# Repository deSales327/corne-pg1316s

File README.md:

# corne-pg1316s

PCB reversível e sem fios no formato **Corne** (3×6 + 3 polegares por metade, 42 teclas)
para os switches ultrafinos **Kailh PG1316S**, com **um LED RGB por tecla** e keycaps impressas
em 3D (do [mikefive](https://github.com/mikeholscher/zmk-config-mikefive)) ou compradas, e **nice!nano + nice!view**. É a versão "irmã" do
[corne-x](https://github.com/deSales327/corne-x), que usa switches Kailh X (PG1425).

| Frente | Verso |
| :---: | :---: |
|  |  |

## Estado
- Roteada nas duas camadas, com plano de GND.
- **DRC do KiCad 10: 0 violações e 0 ligações em falta.**
- Gerbers e furação prontos em [`corne-pg1316s-gerbers.zip`](corne-pg1316s-gerbers.zip).
- **Ainda não foi fabricada nem testada.** Há footprints de PG1316S já fabricados com os contactos em sítios diferentes: x = ±2,5 mm (ficha técnica, [mikefive](https://github.com/mikeholscher/zmk-config-mikefive), [ULK](https://github.com/Goga64/ULK)) e x = −0,5 / +1,7 mm ([Delta Omega](https://github.com/unspecworks/delta-omega) rev4). Os terminais do switch são largos o suficiente para os dois. Mesmo assim, confirma com um switch físico (por exemplo, numa impressão 1:1) antes de encomendar.
- **v0.5:** o XIAO deu lugar a um Pro Micro nRF52840 (nice!nano v2 ou clone) com a pinagem do Corne do ZMK, e há furos para um nice!view por cima dele. Os LEDs são desligados por software (VCC do nice!nano), por isso o interruptor RGB1 saiu. Foi acrescentado um botão de reset. Usa os gerbers da v0.5.
- **v0.4:** um LED RGB WS2812B-2020 por tecla, na cavidade debaixo do switch. Os díodos passaram para o intervalo entre colunas, na face de baixo.
- **v0.3:** os pads de contacto são largos e cobrem as duas posições testadas: o pad 1 vai de −3,275 a −0,025 mm e o pad 2 de +0,925 a +3,275 mm, como no footprint reversível do mikefive. No verso ficam espelhados.

## Componentes (por metade)
| Qtd. | Peça |
|---|---|
| 21 | Kailh PG1316S (SMD) |
| 21 | LED RGB WS2812B-2020 (2 × 2 mm) |
| 21 | Díodo 1N4148W, SOD-123 |
| 1 | Pro Micro nRF52840: nice!nano v2 ou clone compatível (ex.: SuperMini nRF52840) com corte de VCC no P0.13 |
| 1 | nice!view (ecrã de 1,08", 36 × 14 mm), com o conector e os pinos que trazem |
| 2 | Barras de 12 pinos fêmea + pinos macho baixos (para o controlador) |
| 1 | Interruptor SPDT (o mesmo do dust) |
| 1 | Botão Omron B3U-1000P (reset) |
| 1 | Conector JST-XH 2,50 mm, vertical, 2 pinos |
| 1 | Bateria LiPo com ficha JST-XH (quanto maior, melhor, por causa dos LEDs) |
| 21 | Keycaps: Kailh PG1316 1U transparentes (16 × 16 mm, ex.: Modulo "Clear") para se ver a luz, ou as impressas de [`keycaps/`](keycaps/) |
| 4+ | Pés de borracha com 1,5 mm ou mais (os díodos ficam por baixo) |

## Diferenças para o corne-x
- **Espaçamento de 17 × 17 mm** para keycaps de 16,5 × 16,5 mm. Cada metade mede 128,5 × 83,9 mm.
- **Footprint PG1316S reversível**, desenhado em `gerar_pcb.py`:
  - O chassi e os furos seguem a ficha técnica `CPG1316S01D02`.
  - Os contactos são largos e cobrem as posições dos footprints testados do mikefive, do ULK e do Delta Omega.
  - Os terminais do switch não são simétricos, por isso os contactos têm pads próprios em cada face, espelhados no verso, e as pistas ligam-nos entre si.
  - Os pads do chassi têm um furo metalizado e servem as duas faces.
  - Há furos para os pinos de alinhamento das duas faces.
- **LED na cavidade debaixo do switch**, que é a janela de LED da ficha técnica. Os pads existem nas duas faces; o LED vai na mesma face que o switch.
- **Díodos entre colunas, na face oposta à do switch** (a de baixo). Os pads existem nas duas faces; na face do switch ficam vazios.
- **Soldadura**, por esta ordem, em cada metade:
  1. LEDs e switches na face de cima (numa metade é a frente, na outra o verso), com pasta de solda e placa de aquecimento (hotplate). Os LEDs de 2 × 2 mm são difíceis de soldar com ferro.
  2. Díodos na face de baixo, com ferro de soldar (não voltes a pôr a placa na hotplate com peças por baixo).
  3. Botão de reset na face de cima, também com ferro.
  4. Controlador, nice!view, interruptor e conector.
  - Testa os LEDs antes de soldar os switches por cima: depois deixam de estar acessíveis.

## Bateria
- **J1**: JST-XH 2,50 mm vertical, de furos passantes. O pino 1 é o BAT+ e o pino 2 o BAT−.
- **H1**: furo de 3,2 mm para passar os fios da bateria, que fica por baixo da placa.
- **PWR1**: interruptor no BAT−.
- O BAT+ liga ao pino RAW do nice!nano v2, que é a entrada da bateria (e passa pelo carregador dele).
- Atenção à altura: o JST-XH vertical tem cerca de 7 mm, muito mais do que o resto do teclado.

## Controlador e nice!view
- **MCU1**: Pro Micro reversível sem pontes de solda. Os furos são os mesmos nas duas faces:
  - na metade em que a placa tem a **frente para cima**, o controlador monta-se com os **componentes para cima**;
  - na metade em que a placa tem o **verso para cima**, monta-se com os **componentes para baixo** (como no Corne). Assim cada pino cai sempre no mesmo furo. Está escrito no silkscreen de cada face.
- **DISP1**: duas filas de 5 furos para o nice!view, logo abaixo do controlador. A fila de cima é para a metade com a frente para cima e a de baixo para a outra (a ordem dos pinos fica invertida quando a placa se vira). O ecrã fica por cima do controlador.
- **RST1**: botão de reset (duplo toque entra no bootloader). Há pads nas duas faces; solda-se só o da face de cima.
- Altura: com o nice!view por cima, o bloco do controlador fica bem mais alto do que as teclas (cerca de 7–10 mm, conforme os pinos e as barras que usares).

## Pinos do Pro Micro
Iguais aos do Corne do ZMK, por isso servem os shields `corne_left`/`corne_right` sem alterações.

| Pino | Função | Pino | Função |
|---|---|---|---|
| D1 (P0.06) | nice!view CS | RAW | BAT+ (via J1) |
| D0 (P0.08) | dados dos LEDs RGB | GND | GND |
| GND | GND | RST | botão de reset |
| GND | GND | VCC | 3,3 V comutado (LEDs e nice!view) |
| D2 (P0.17) | nice!view MOSI | D21 | c0 (mindinho externo) |
| D3 (P0.20) | nice!view SCK | D20 | c1 (mindinho) |
| D4 | r3 (fila de cima) | D19 | c2 (anelar) |
| D5 | r2 (fila home) | D18 | c3 (médio) |
| D6 | r1 (fila de baixo) | D15 | c4 (indicador) |
| D7 | r0 (polegares) | D14 | c5 (indicador interno) |
| D8 | livre | D16 | livre |
| D9 | livre | D10 | livre |

- O cátodo dos díodos (pad 1) fica na linha: COL2ROW, como no Corne.
- Os polegares usam as colunas c3, c4 e c5 da linha r0 (`RC(3,3)`, `RC(3,4)`, `RC(3,5)`).

## LEDs RGB
- **L1–L21**: WS2812B-2020, um por tecla, em cadeia: D0 → polegares (de dentro para fora) → colunas em serpentina, da interna (c5) para a externa (c0).
- Alimentados pelo **VCC do nice!nano** (3,3 V), que o ZMK corta quando os LEDs estão desligados ou o teclado em repouso (`ext-power`, P0.13). Os LEDs gastam corrente mesmo apagados, por isso este corte é importante.
- 3,3 V está abaixo dos 3,7 V da ficha técnica dos WS2812B-2020. É como muitos Corne sem fios com nice!nano funcionam, mas o azul e o branco podem ficar um pouco mais fracos.
- **Limita o brilho no firmware.** O VCC do nice!nano não aguenta os 21 LEDs a branco no máximo.

## ZMK
No `build.yaml` do teu zmk-config:

```yaml
include:
  - board: nice_nano_v2
    shield: corne_left nice_view_adapter nice_view
  - board: nice_nano_v2
    shield: corne_right nice_view_adapter nice_view
```

(Nas versões mais recentes do ZMK a placa chama-se `nice_nano` em vez de `nice_nano_v2`.)

Para os LEDs, num `corne.overlay` (ou `corne_left.overlay` e `corne_right.overlay`) na pasta `config`:

```dts
#include <dt-bindings/led/led.h>

&pinctrl {
    spi3_default: spi3_default {
        group1 { psels = <NRF_PSEL(SPIM_MOSI, 0, 8)>; };
    };
    spi3_sleep: spi3_sleep {
        group1 { psels = <NRF_PSEL(SPIM_MOSI, 0, 8)>; low-power-enable; };
    };
};

&spi3 {
    compatible = "nordic,nrf-spim";
    status = "okay";
    pinctrl-0 = <&spi3_default>;
    pinctrl-1 = <&spi3_sleep>;
    pinctrl-names = "default", "sleep";
    led_strip: ws2812@0 {
        compatible = "worldsemi,ws2812-spi";
        reg = <0>;
        spi-max-frequency = <4000000>;
        chain-length = <21>;
        spi-one-frame = <0x70>;
        spi-zero-frame = <0x40>;
        color-mapping = <LED_COLOR_ID_GREEN LED_COLOR_ID_RED LED_COLOR_ID_BLUE>;
    };
};

/ { chosen { zmk,underglow = &led_strip; }; };
```

No `corne.conf`:

```
CONFIG_ZMK_RGB_UNDERGLOW=y
CONFIG_WS2812_STRIP=y
CONFIG_ZMK_RGB_UNDERGLOW_EXT_POWER=y
CONFIG_ZMK_RGB_UNDERGLOW_BRT_MAX=40
CONFIG_ZMK_RGB_UNDERGLOW_AUTO_OFF_IDLE=y
```
## Regenerar
```
python gerar_pcb.py caminho/para/dust/pcbs/dust.kicad_pcb
"%LOCALAPPDATA%\Programs\KiCad\10.0\bin\python.exe" finalizar_pcb.py caminho/para/freerouting-2.5.0.jar
python mockup.py
```
Precisas do `shapely` (pip), do KiCad 10, do Freerouting 2.5 e do Java 25.

## Créditos
- Díodo e interruptor: [dust](https://github.com/hazels-garage/dust), de Jason Hazel (CC BY 4.0).
- Keycaps e referência do PG1316S: [mikefive](https://github.com/mikeholscher/zmk-config-mikefive), de Mike Holscher. Uso permitido com crédito ao autor.
- Footprint do switch: desenhado a partir da ficha técnica da Kailh (CPG1316S01D02). As posições dos contactos foram comparadas com o [Delta Omega](https://github.com/unspecworks/delta-omega), de unspecworks (CERN-OHL-W-2.0), e com o [ULK](https://github.com/Goga64/ULK), de Georgii Miakishev (MIT), um Corne com PG1316S já construído.
- Lojas de PG1316S indicadas pelo Delta Omega (não verificadas): Modulo Industries (EUA), Holykeebs (EUA) e Keycapsss (UE).
- Layout: Corne (crkbd), de foostan (MIT).
- Este projeto: CC BY 4.0, exceto as keycaps, que seguem as condições do autor.

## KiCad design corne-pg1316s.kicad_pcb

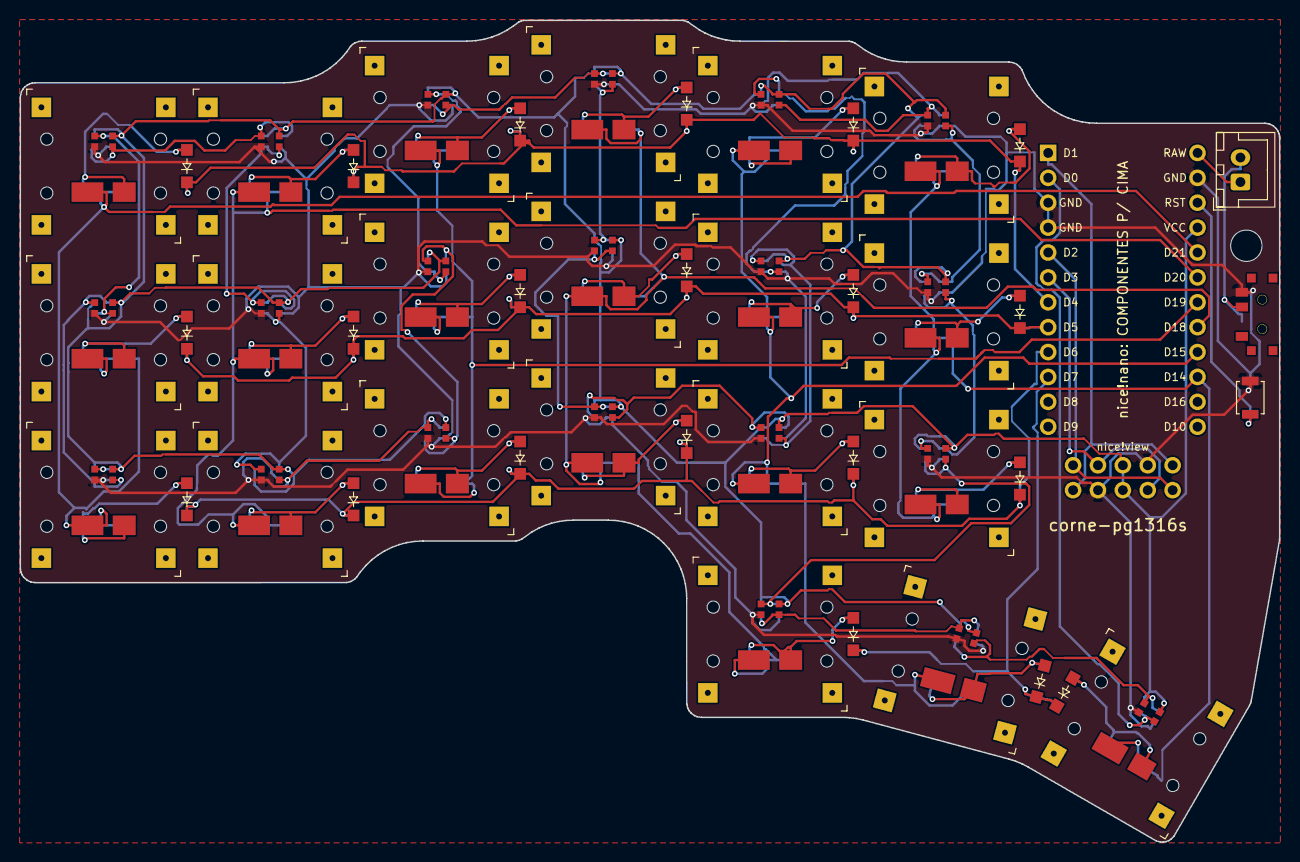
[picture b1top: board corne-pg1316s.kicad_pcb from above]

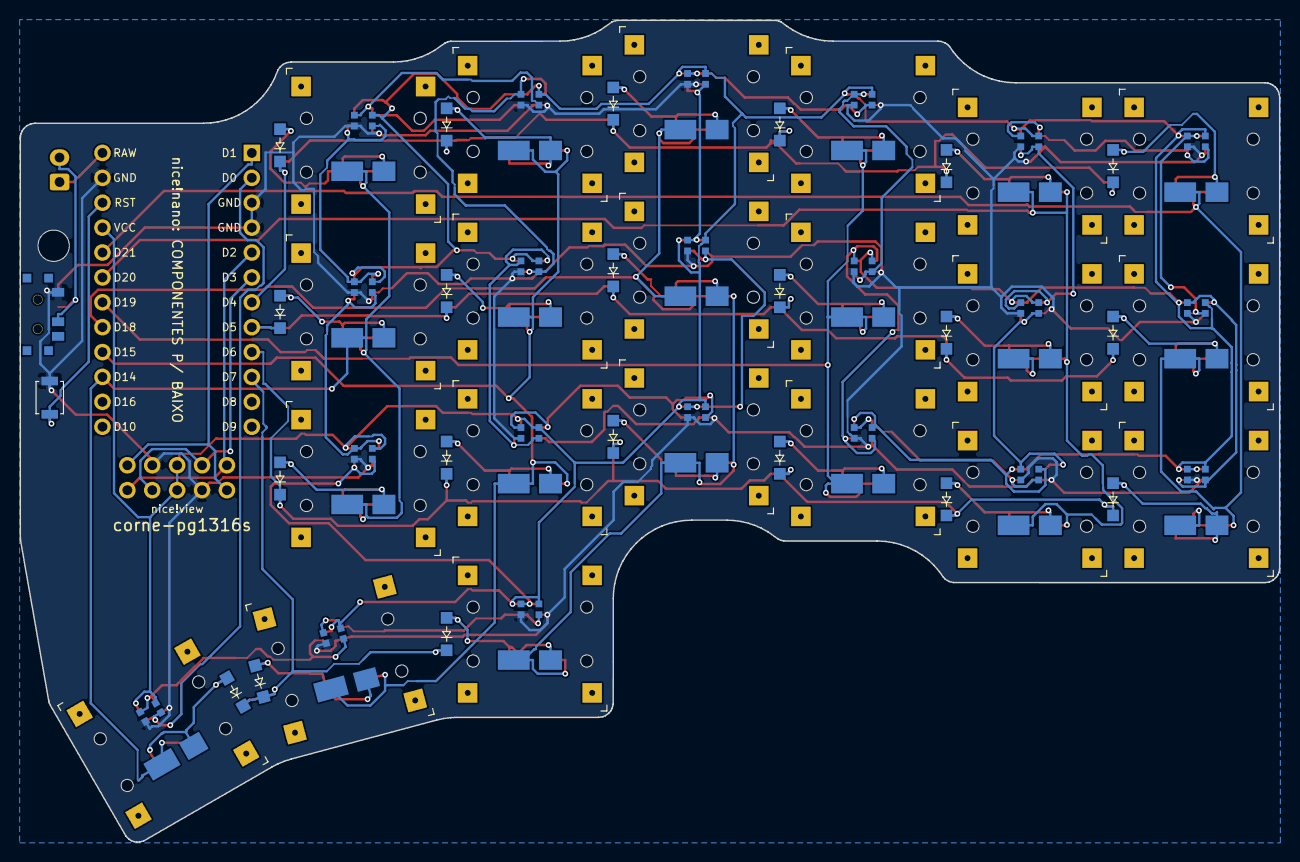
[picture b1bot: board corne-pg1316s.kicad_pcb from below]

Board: 2 copper layers, 128.5 x 83.9 mm, 71 parts (2 on the bottom side), 60 nets.

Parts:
D1, D2, D3, D4, D5, D6, D7, D8, D9, D10, D11, D12, D13, D14, D15, D16, D17, D18, D19, D20, D21: ComboDiode
DISP1: nice_view_reversible
H1: MountingHole_3.2mm_M3
J1: JST_XH_B2B-XH-A_1x02_P2.50mm_Vertical
L1, L2, L3, L4, L5, L6, L7, L8, L9, L10, L11, L12, L13, L14, L15, L16, L17, L18, L19, L20, L21: WS2812B-2020; WS2812B-2020_reversible
MCU1: ProMicro_reversible
PWR1, PWR1#2: SPDT_C128955
RST1, RST2: SW_SPST_B3U-1000P
S1, S2, S3, S4, S5, S6, S7, S8, S9, S10, S11, S12, S13, S14, S15, S16, S17, S18, S19, S20, S21: PG1316S; Kailh_PG1316S_reversible

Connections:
BAT: J1.1, MCU1.13
BAT-: J1.2, PWR1.2, PWR1#2.2
GND: DISP1.4, DISP1.7, L1.2, L2.2, L3.2, L4.2, L5.2, L6.2, L7.2, L8.2, L9.2, L10.2, L11.2, L12.2, L13.2, L14.2, L15.2, L16.2, L17.2, L18.2, L19.2, L20.2, L21.2, MCU1.3, MCU1.4, MCU1.14, PWR1.3, PWR1#2.1, RST1.2, RST2.2
RST: MCU1.15, RST1.1, RST2.1
VCC: DISP1.3, DISP1.8, L1.4, L2.4, L3.4, L4.4, L5.4, L6.4, L7.4, L8.4, L9.4, L10.4, L11.4, L12.4, L13.4, L14.4, L15.4, L16.4, L17.4, L18.4, L19.4, L20.4, L21.4, MCU1.16
c0: MCU1.17, S1.1, S2.1, S3.1
c1: MCU1.18, S4.1, S5.1, S6.1
c2: MCU1.19, S7.1, S8.1, S9.1
c3: MCU1.20, S10.1, S11.1, S12.1, S19.1
c4: MCU1.21, S13.1, S14.1, S15.1, S20.1
c5: MCU1.22, S16.1, S17.1, S18.1, S21.1
k_c0_r1: D3.2, S3.2
k_c0_r2: D2.2, S2.2
k_c0_r3: D1.2, S1.2
k_c1_r1: D6.2, S6.2
k_c1_r2: D5.2, S5.2
k_c1_r3: D4.2, S4.2
k_c2_r1: D9.2, S9.2
k_c2_r2: D8.2, S8.2
k_c2_r3: D7.2, S7.2
k_c3_r0: D19.2, S19.2
k_c3_r1: D12.2, S12.2
k_c3_r2: D11.2, S11.2
k_c3_r3: D10.2, S10.2
k_c4_r0: D20.2, S20.2
k_c4_r1: D15.2, S15.2
k_c4_r2: D14.2, S14.2
k_c4_r3: D13.2, S13.2
k_c5_r0: D21.2, S21.2
k_c5_r1: D18.2, S18.2
k_c5_r2: D17.2, S17.2
k_c5_r3: D16.2, S16.2
nv_cs: DISP1.5, DISP1.6, MCU1.1
nv_mosi: DISP1.1, DISP1.10, MCU1.5
nv_sck: DISP1.2, DISP1.9, MCU1.6
r0: D19.1, D20.1, D21.1, MCU1.10
r1: D3.1, D6.1, D9.1, D12.1, D15.1, D18.1, MCU1.9
r2: D2.1, D5.1, D8.1, D11.1, D14.1, D17.1, MCU1.8
r3: D1.1, D4.1, D7.1, D10.1, D13.1, D16.1, MCU1.7
rgb0: L21.3, MCU1.2
rgb1: L20.3, L21.1
rgb2: L19.3, L20.1
rgb3: L18.3, L19.1
rgb4: L17.3, L18.1
rgb5: L16.3, L17.1
rgb6: L13.3, L16.1
rgb7: L13.1, L14.3
rgb8: L14.1, L15.3
rgb9: L12.3, L15.1
rgb10: L11.3, L12.1
rgb11: L10.3, L11.1
rgb12: L7.3, L10.1
rgb13: L7.1, L8.3
rgb14: L8.1, L9.3
rgb15: L6.3, L9.1
rgb16: L5.3, L6.1
rgb17: L4.3, L5.1
rgb18: L1.3, L4.1
rgb19: L1.1, L2.3
rgb20: L2.1, L3.3
